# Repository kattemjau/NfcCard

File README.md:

# NfcCard
Just a simple nfc card made in pcb for use as a buseniss card

Inspired by:
https://www.instructables.com/id/PCB-Business-Card-With-NFC/

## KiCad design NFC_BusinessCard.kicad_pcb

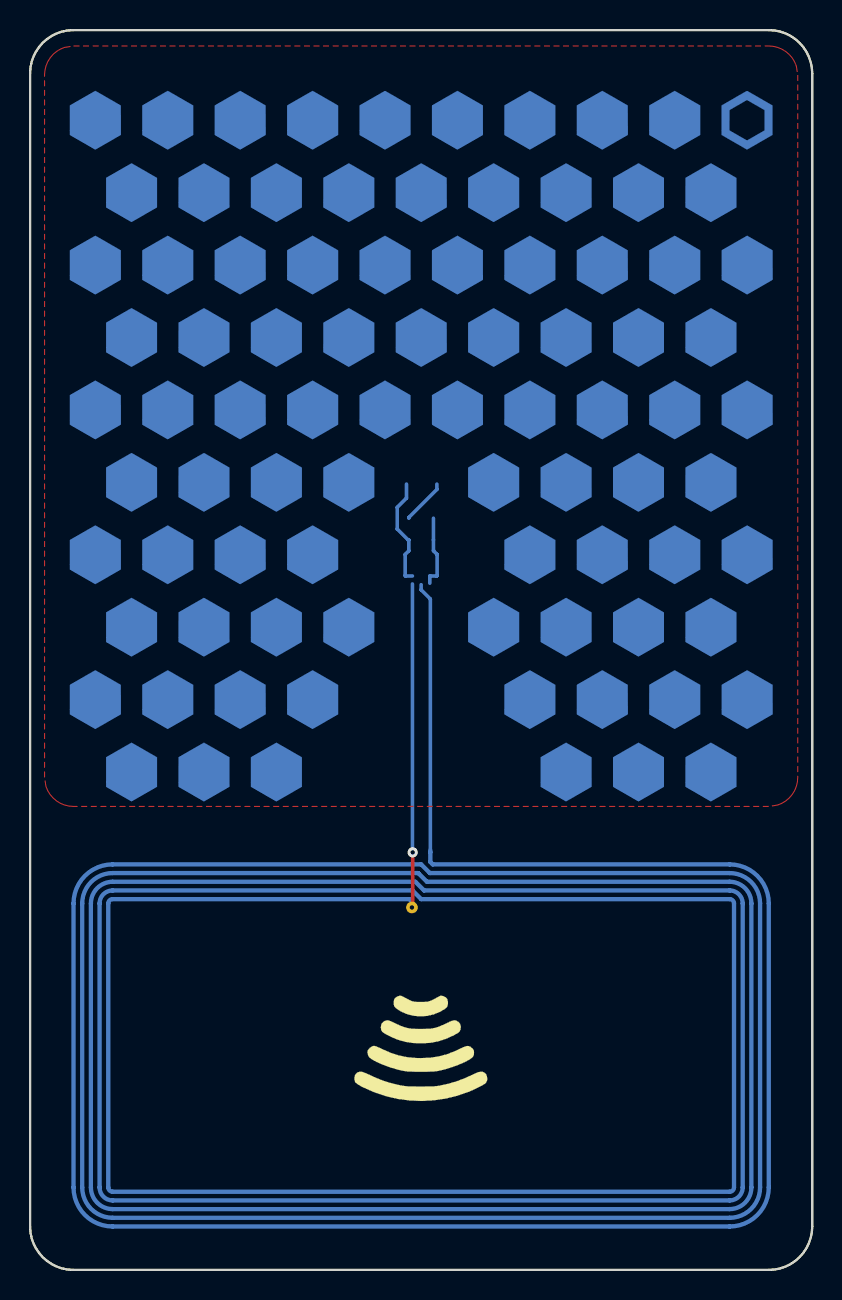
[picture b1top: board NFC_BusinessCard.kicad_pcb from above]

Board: 2 copper layers, 54.0 x 85.6 mm, 5 parts (0 on the bottom side), 5 nets.

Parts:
ANT1: 25X48MM_NFC_ANTENNA; 25X48MM_NFC
C1: 220 nf; C0603
LED1: LEDSML0805; SML0805
NT3H1101: NT3H; XQFN8
R1: 47 Ω; R0603

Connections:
unnamed: ANT1.P$1, NT3H1101.LB
unnamed: ANT1.P$2, NT3H1101.LA
unnamed: C1.1, NT3H1101.VCC, NT3H1101.VOUT, R1.1
unnamed: C1.2, LED1.C, NT3H1101.VSS
unnamed: LED1.A, R1.2

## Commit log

2019-05-15 NFC pcb card
